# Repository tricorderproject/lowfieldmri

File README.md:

lowfieldmri
======

Experiments in Earth's field magnetic resonance imaging<br>

**DISCLAIMER OF WARRANTIES AND LIMITATION OF LIABILITY.**

UNLESS OTHERWISE SEPARATELY UNDERTAKEN BY THE LICENSOR, TO THE MAXIMUM EXTENT POSSIBLE, THE LICENSOR OFFERS THE LICENSED MATERIAL AS-IS AND AS-AVAILABLE, AND MAKES NO REPRESENTATIONS OR WARRANTIES OF ANY KIND CONCERNING THE LICENSED MATERIAL, WHETHER EXPRESS, IMPLIED, STATUTORY, OR OTHER. THIS INCLUDES, WITHOUT LIMITATION, WARRANTIES OF TITLE, MERCHANTABILITY, FITNESS FOR A PARTICULAR PURPOSE, NON-INFRINGEMENT, ABSENCE OF LATENT OR OTHER DEFECTS, ACCURACY, SAFETY, OR THE PRESENCE OR ABSENCE OF ERRORS, WHETHER OR NOT KNOWN OR DISCOVERABLE. WHERE DISCLAIMERS OF WARRANTIES ARE NOT ALLOWED IN FULL OR IN PART, THIS DISCLAIMER MAY NOT APPLY TO YOU.

TO THE EXTENT POSSIBLE, IN NO EVENT WILL THE LICENSOR BE LIABLE TO YOU ON ANY LEGAL THEORY (INCLUDING, WITHOUT LIMITATION, NEGLIGENCE) OR OTHERWISE FOR ANY DIRECT, SPECIAL, INDIRECT, INCIDENTAL, CONSEQUENTIAL, PUNITIVE, EXEMPLARY, OR OTHER LOSSES, COSTS, EXPENSES, OR DAMAGES ARISING OUT OF THIS PUBLIC LICENSE OR USE OF THE LICENSED MATERIAL, EVEN IF THE LICENSOR HAS BEEN ADVISED OF THE POSSIBILITY OF SUCH LOSSES, COSTS, EXPENSES, OR DAMAGES. WHERE A LIMITATION OF LIABILITY IS NOT ALLOWED IN FULL OR IN PART, THIS LIMITATION MAY NOT APPLY TO YOU.

THE DISCLAIMER OF WARRANTIES AND LIMITATION OF LIABILITY PROVIDED ABOVE SHALL BE INTERPRETED IN A MANNER THAT, TO THE EXTENT POSSIBLE, MOST CLOSELY APPROXIMATES AN ABSOLUTE DISCLAIMER AND WAIVER OF ALL LIABILITY.

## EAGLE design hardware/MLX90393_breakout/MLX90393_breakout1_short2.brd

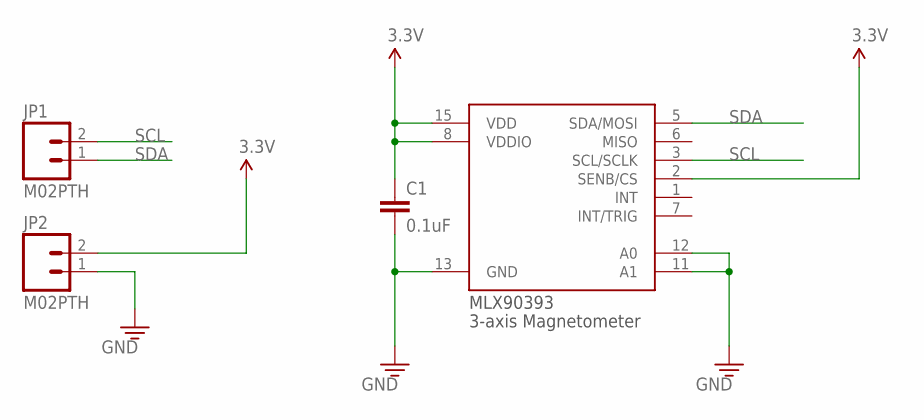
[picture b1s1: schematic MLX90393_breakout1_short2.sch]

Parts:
C1: 0.1uF; 0603
JP1, JP2: M02PTH; 1X02
U$1: MLX90393; 16-QFN

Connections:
3.3V: C1.1, JP2.2, U$1.2 (SENB/CS), U$1.8 (VDDIO), U$1.15 (VDD)
GND: C1.2, JP2.1, U$1.11 (A1), U$1.12 (A0), U$1.13 (GND)
SCL: JP1.2, U$1.3 (SCL/SCLK)
SDA: JP1.1, U$1.5 (SDA/MOSI)

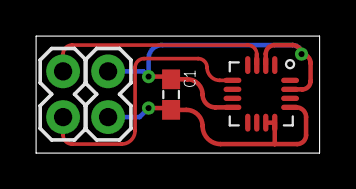
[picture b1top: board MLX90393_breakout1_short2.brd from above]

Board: 2 copper layers, 15.8 x 6.5 mm, 4 parts (0 on the bottom side), 4 nets.

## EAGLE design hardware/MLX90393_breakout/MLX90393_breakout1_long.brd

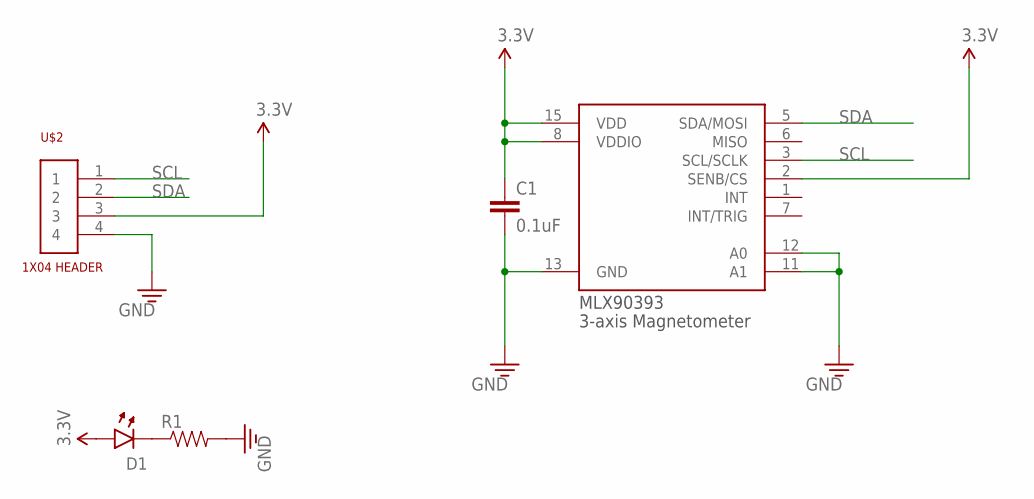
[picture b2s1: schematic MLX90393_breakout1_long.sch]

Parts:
C1: 0.1uF; 0603
D1: 0605-LED; 0603-LED
R1: RESISTOR0603; 0603
U$1: MLX90393; 16-QFN
U$2: 1X04

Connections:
3.3V: C1.1, D1.ANODE, U$1.2 (SENB/CS), U$1.8 (VDDIO), U$1.15 (VDD), U$2.3
GND: C1.2, R1.2, U$1.11 (A1), U$1.12 (A0), U$1.13 (GND), U$2.4
unnamed: D1.CATHODE, R1.1
SCL: U$1.3 (SCL/SCLK), U$2.1
SDA: U$1.5 (SDA/MOSI), U$2.2

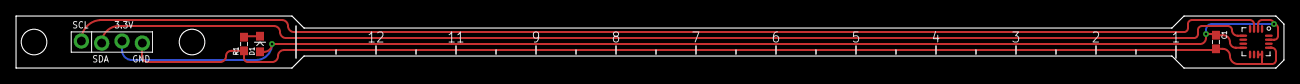
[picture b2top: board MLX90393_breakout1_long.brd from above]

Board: 2 copper layers, 158.5 x 6.5 mm, 5 parts (0 on the bottom side), 5 nets.

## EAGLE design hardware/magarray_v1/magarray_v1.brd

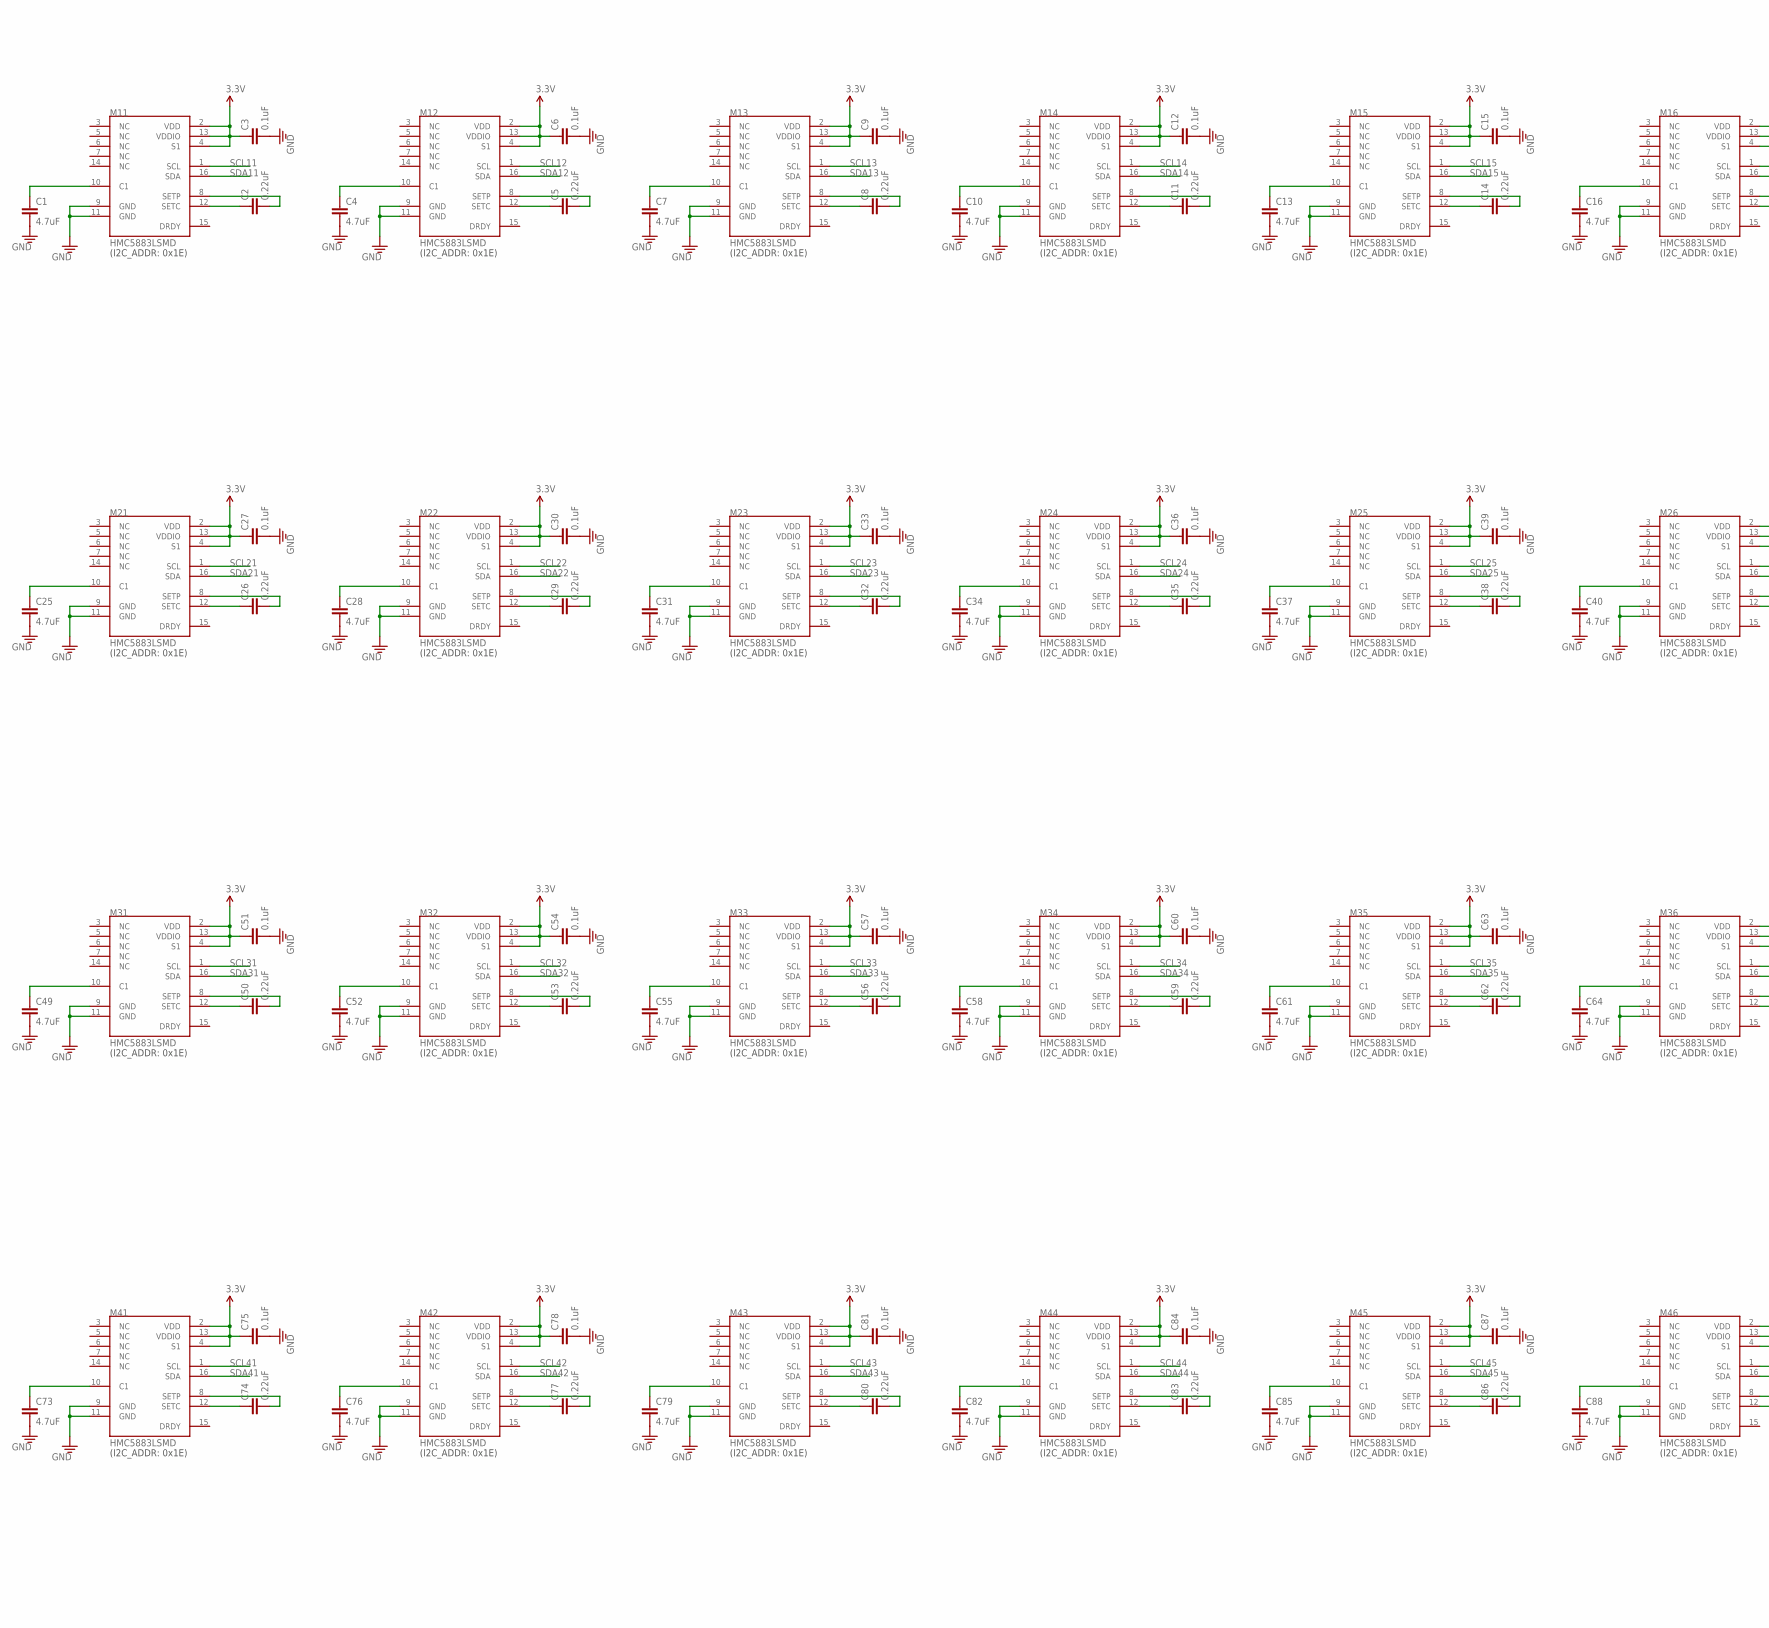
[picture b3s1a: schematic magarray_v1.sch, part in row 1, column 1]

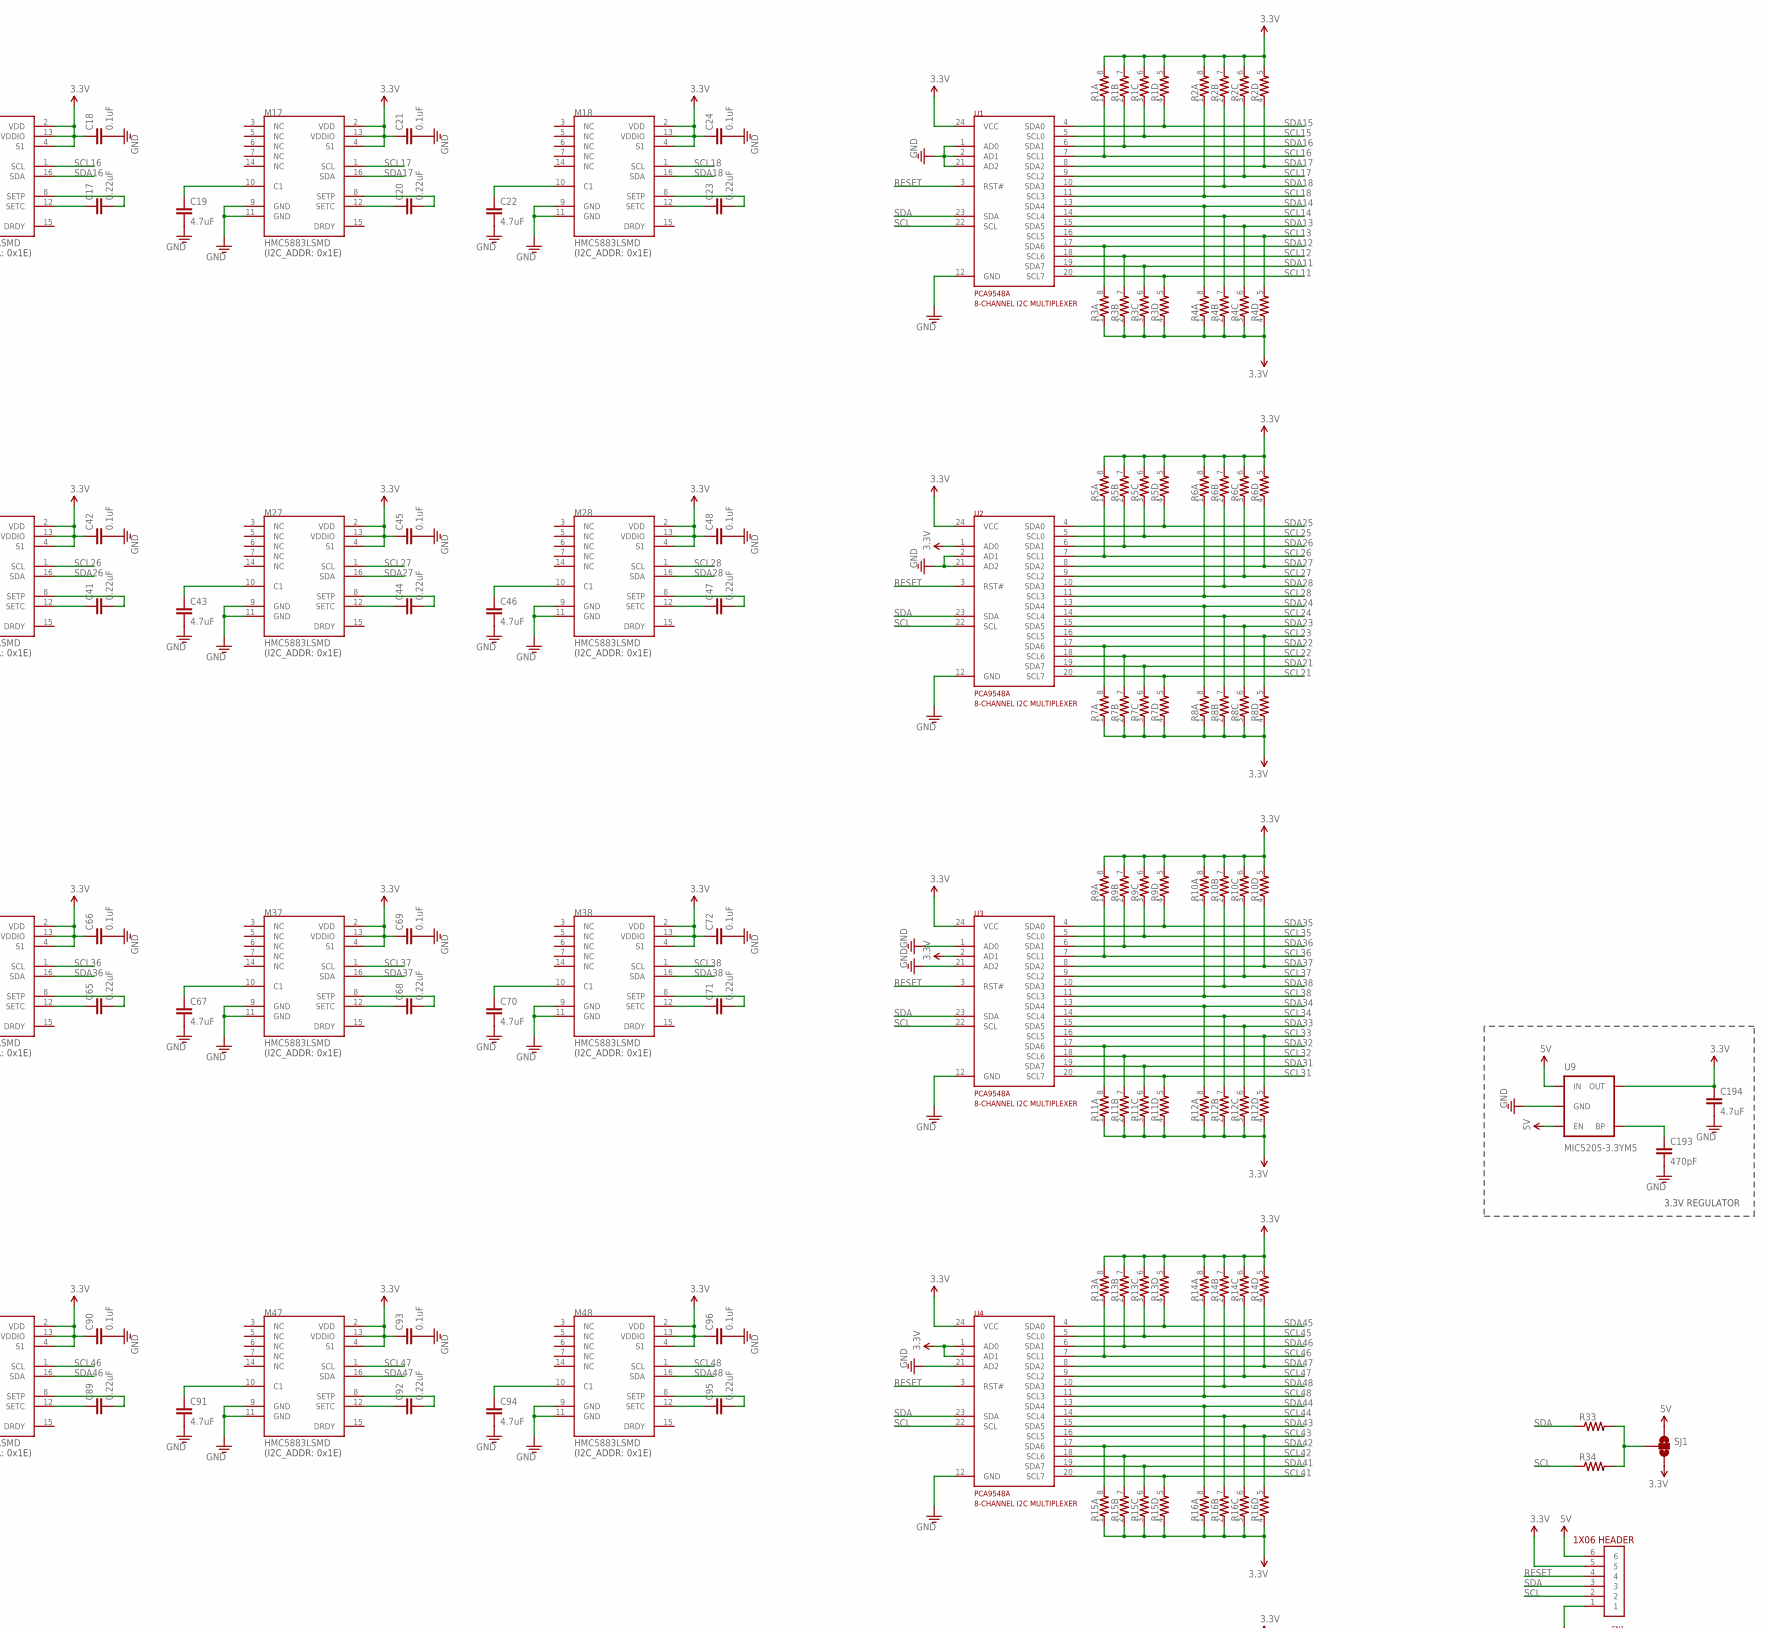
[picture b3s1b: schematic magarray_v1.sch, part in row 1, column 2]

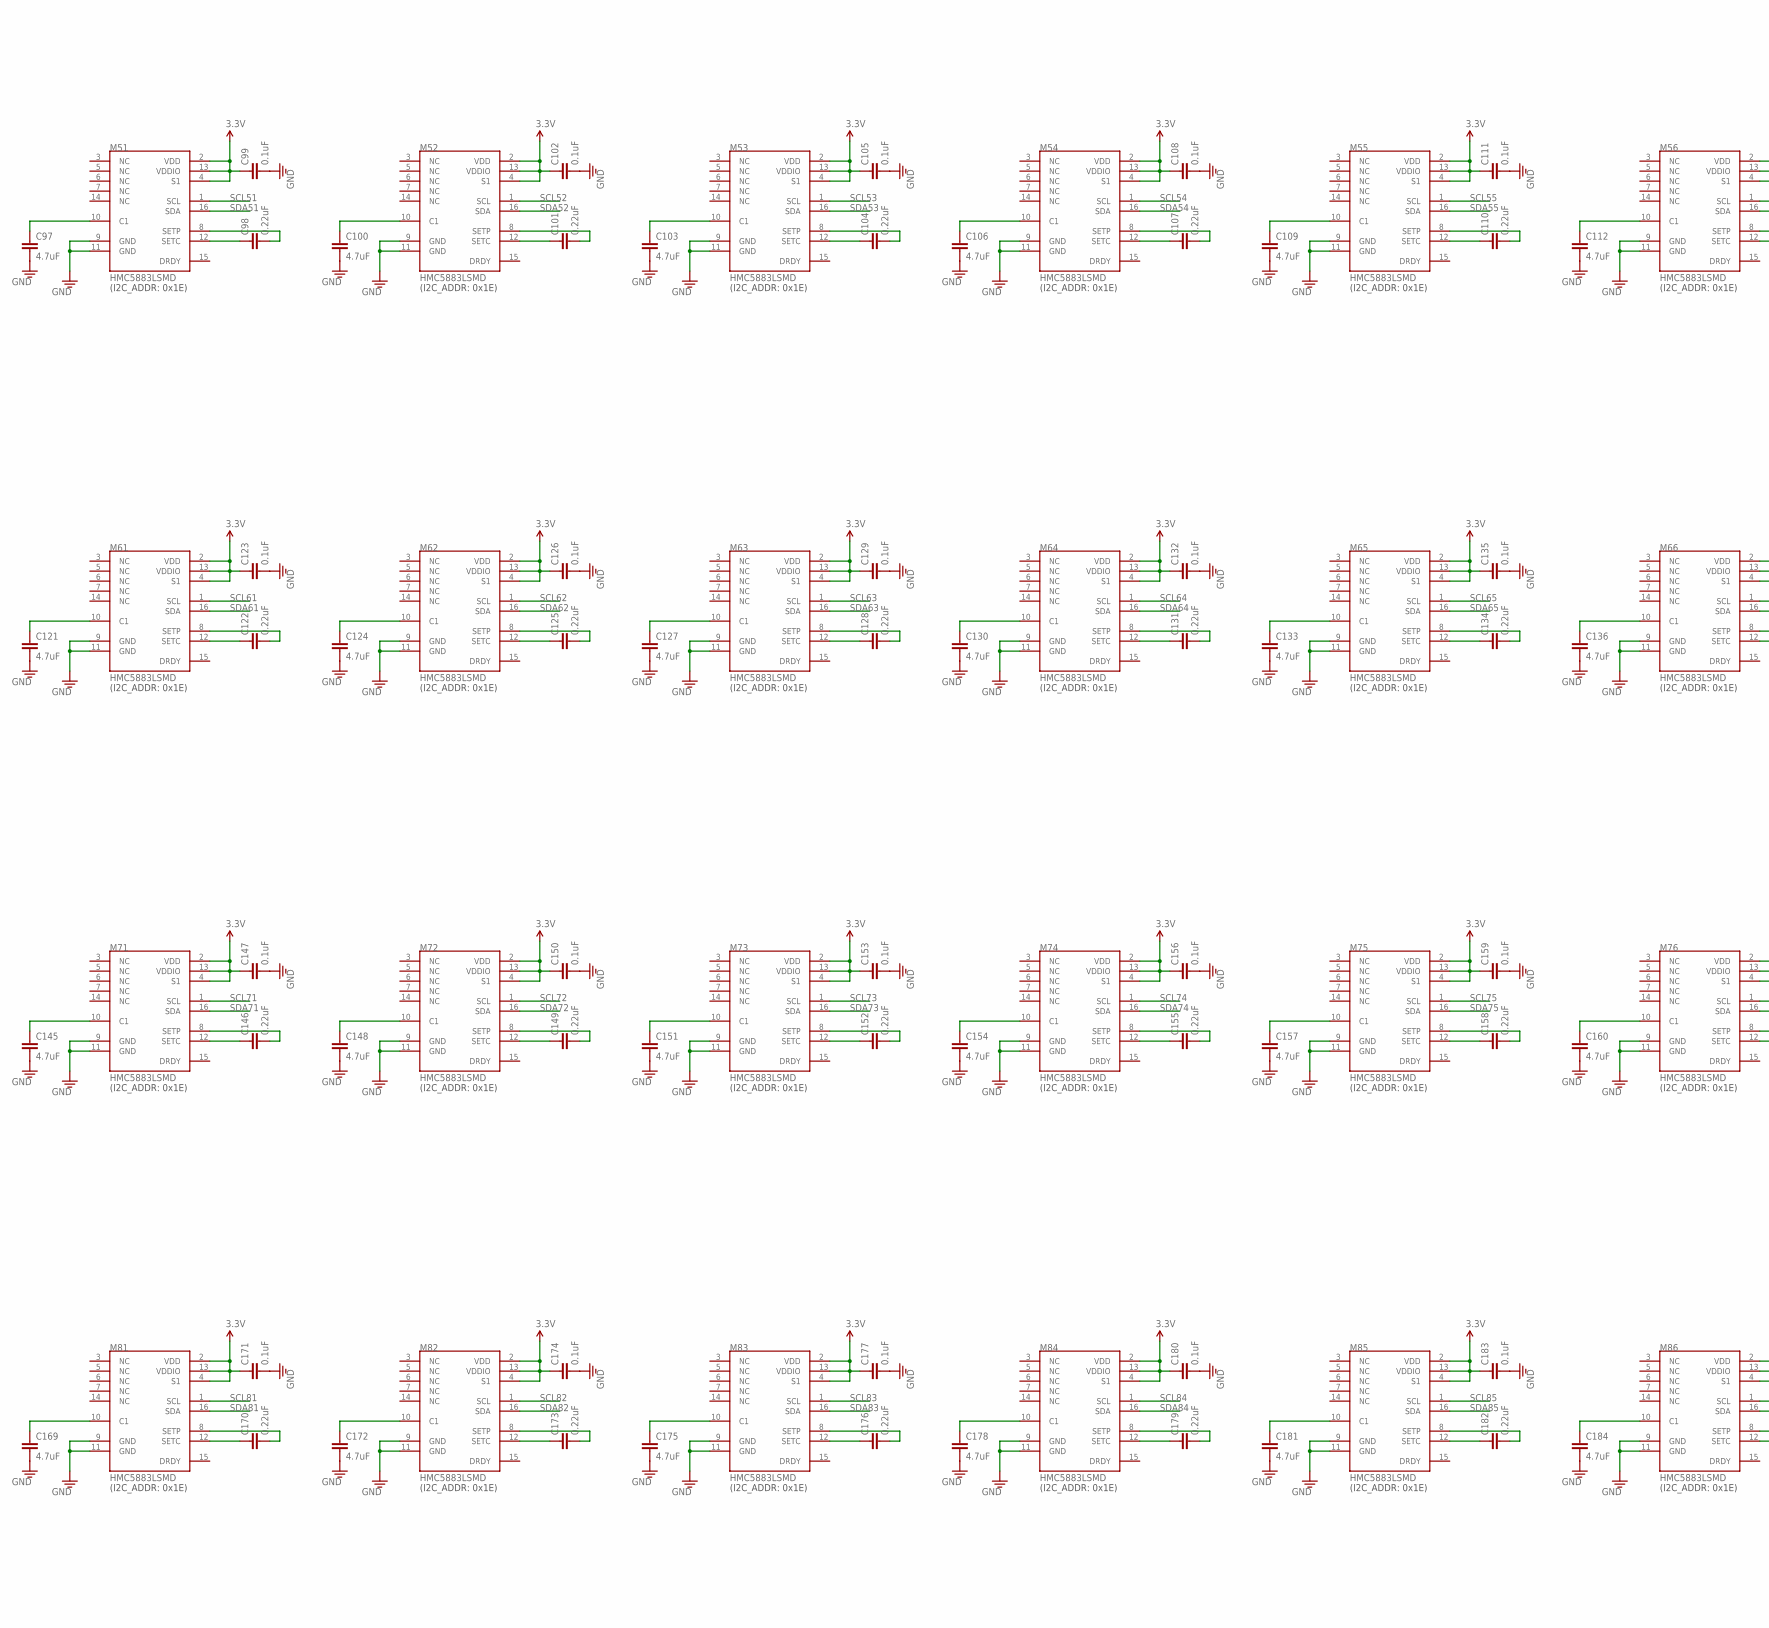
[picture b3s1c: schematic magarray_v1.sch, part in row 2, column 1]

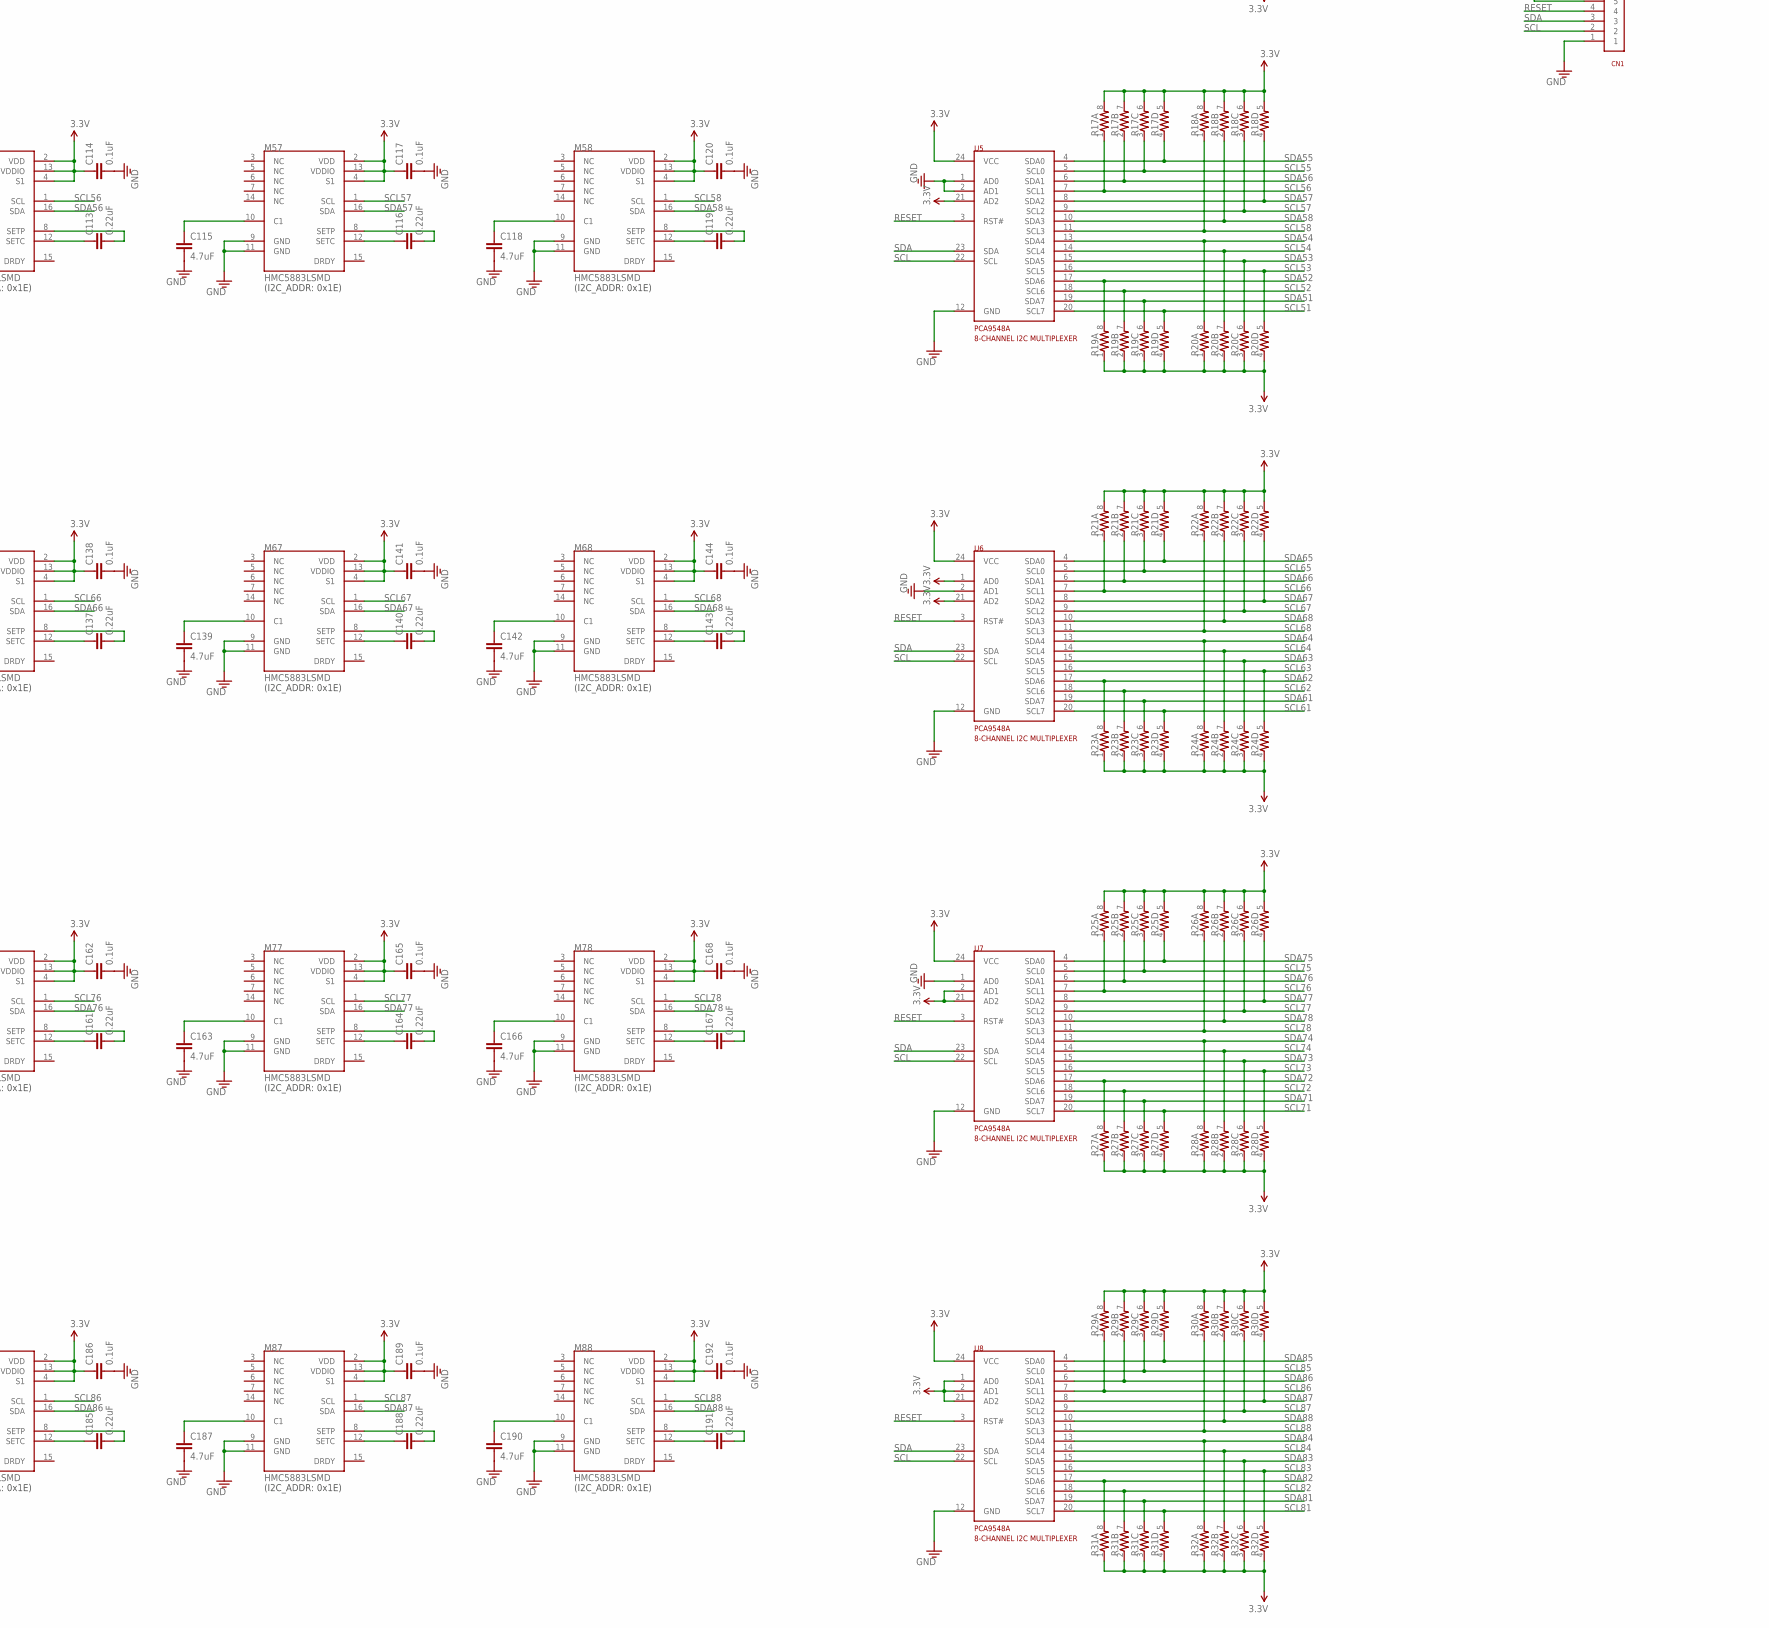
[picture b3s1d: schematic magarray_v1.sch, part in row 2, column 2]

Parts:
C1, C4, C7, C10, C13, C16, C19, C22, C25, C28, C31, C34, C37, C40, C43, C46, C49, C52, C55, C58, C61, C64, C67, C70, C73, C76, C79, C82, C85, C88, C91, C94, C97, C100, C103, C106, C109, C112, C115, C118, C121, C124, C127, C130, C133, C136, C139, C142, C145, C148, C151, C154, C157, C160, C163, C166, C169, C172, C175, C178, C181, C184, C187, C190: 4.7uF; 0603
C2, C5, C8, C11, C14, C17, C20, C23, C26, C29, C32, C35, C38, C41, C44, C47, C50, C53, C56, C59, C62, C65, C68, C71, C74, C77, C80, C83, C86, C89, C92, C95, C98, C101, C104, C107, C110, C113, C116, C119, C122, C125, C128, C131, C134, C137, C140, C143, C146, C149, C152, C155, C158, C161, C164, C167, C170, C173, C176, C179, C182, C185, C188, C191: 0.22uF; C0402
C3, C6, C9, C12, C15, C18, C21, C24, C27, C30, C33, C36, C39, C42, C45, C48, C51, C54, C57, C60, C63, C66, C69, C72, C75, C78, C81, C84, C87, C90, C93, C96, C99, C102, C105, C108, C111, C114, C117, C120, C123, C126, C129, C132, C135, C138, C141, C144, C147, C150, C153, C156, C159, C162, C165, C168, C171, C174, C177, C180, C183, C186, C189, C192: 0.1uF; C0402
C193: 470pF; C0402
C194: 4.7uF; C0402
CN1: 1X06
M11, M12, M13, M14, M15, M16, M17, M18, M21, M22, M23, M24, M25, M26, M27, M28, M31, M32, M33, M34, M35, M36, M37, M38, M41, M42, M43, M44, M45, M46, M47, M48, M51, M52, M53, M54, M55, M56, M57, M58, M61, M62, M63, M64, M65, M66, M67, M68, M71, M72, M73, M74, M75, M76, M77, M78, M81, M82, M83, M84, M85, M86, M87, M88: HMC5883LSMD; 16LPCC
R1, R2, R3, R4, R5, R6, R7, R8, R9, R10, R11, R12, R13, R14, R15, R16, R17, R18, R19, R20, R21, R22, R23, R24, R25, R26, R27, R28, R29, R30, R31, R32: RESISTOR-ARRAY0603-ARV; 0603-ARV
R33, R34: RESISTOR0603; 0603
SJ1: SOLDERJUMPER_2WAYPASTE1&2; SJ_3_PASTE1&2
U1, U2, U3, U4, U5, U6, U7, U8: TCA9548A; TSSOP-24-4.4MM
U9: MIC5205-3.3YM5; SOT23-5

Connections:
3.3V: C3.1, C6.1, C9.1, C12.1, C15.1, C18.1, C21.1, C24.1, C27.1, C30.1, C33.1, C36.1, C39.1, C42.1, C45.1, C48.1, C51.1, C54.1, C57.1, C60.1, C63.1, C66.1, C69.1, C72.1, C75.1, C78.1, C81.1, C84.1, C87.1, C90.1, C93.1, C96.1, C99.1, C102.1, C105.1, C108.1, C111.1, C114.1, C117.1, C120.1, C123.1, C126.1, C129.1, C132.1, C135.1, C138.1, C141.1, C144.1, C147.1, C150.1, C153.1, C156.1, C159.1, C162.1, C165.1, C168.1, C171.1, C174.1, C177.1, C180.1, C183.1, C186.1, C189.1, C192.1, C194.1, CN1.5, M11.2 (VDD), M11.4 (S1), M11.13 (VDDIO), M12.2 (VDD), M12.4 (S1), M12.13 (VDDIO), M13.2 (VDD), M13.4 (S1), M13.13 (VDDIO), M14.2 (VDD), M14.4 (S1), M14.13 (VDDIO), M15.2 (VDD), M15.4 (S1), M15.13 (VDDIO), M16.2 (VDD), M16.4 (S1), M16.13 (VDDIO), M17.2 (VDD), M17.4 (S1), M17.13 (VDDIO), M18.2 (VDD), M18.4 (S1), M18.13 (VDDIO), M21.2 (VDD), M21.4 (S1), M21.13 (VDDIO), M22.2 (VDD), M22.4 (S1), M22.13 (VDDIO), M23.2 (VDD), M23.4 (S1), M23.13 (VDDIO), M24.2 (VDD), M24.4 (S1), M24.13 (VDDIO), M25.2 (VDD), M25.4 (S1), M25.13 (VDDIO), M26.2 (VDD), M26.4 (S1), M26.13 (VDDIO), M27.2 (VDD), M27.4 (S1), M27.13 (VDDIO), M28.2 (VDD), M28.4 (S1), M28.13 (VDDIO), M31.2 (VDD), M31.4 (S1), M31.13 (VDDIO), M32.2 (VDD), M32.4 (S1), M32.13 (VDDIO), M33.2 (VDD), M33.4 (S1), M33.13 (VDDIO), M34.2 (VDD), M34.4 (S1), M34.13 (VDDIO), M35.2 (VDD), M35.4 (S1), M35.13 (VDDIO), M36.2 (VDD), M36.4 (S1), M36.13 (VDDIO), M37.2 (VDD), M37.4 (S1), M37.13 (VDDIO), M38.2 (VDD), M38.4 (S1), M38.13 (VDDIO), M41.2 (VDD), M41.4 (S1), M41.13 (VDDIO), M42.2 (VDD), M42.4 (S1), M42.13 (VDDIO), M43.2 (VDD), M43.4 (S1), M43.13 (VDDIO), M44.2 (VDD), M44.4 (S1), M44.13 (VDDIO), M45.2 (VDD), M45.4 (S1), M45.13 (VDDIO), M46.2 (VDD), M46.4 (S1), M46.13 (VDDIO), M47.2 (VDD), M47.4 (S1), M47.13 (VDDIO), M48.2 (VDD)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
5V: CN1.6, SJ1.1, U9.1 (IN), U9.3 (EN)
GND: C1.2, C3.2, C4.2, C6.2, C7.2, C9.2, C10.2, C12.2, C13.2, C15.2, C16.2, C18.2, C19.2, C21.2, C22.2, C24.2, C25.2, C27.2, C28.2, C30.2, C31.2, C33.2, C34.2, C36.2, C37.2, C39.2, C40.2, C42.2, C43.2, C45.2, C46.2, C48.2, C49.2, C51.2, C52.2, C54.2, C55.2, C57.2, C58.2, C60.2, C61.2, C63.2, C64.2, C66.2, C67.2, C69.2, C70.2, C72.2, C73.2, C75.2, C76.2, C78.2, C79.2, C81.2, C82.2, C84.2, C85.2, C87.2, C88.2, C90.2, C91.2, C93.2, C94.2, C96.2, C97.2, C99.2, C100.2, C102.2, C103.2, C105.2, C106.2, C108.2, C109.2, C111.2, C112.2, C114.2, C115.2, C117.2, C118.2, C120.2, C121.2, C123.2, C124.2, C126.2, C127.2, C129.2, C130.2, C132.2, C133.2, C135.2, C136.2, C138.2, C139.2, C141.2, C142.2, C144.2, C145.2, C147.2, C148.2, C150.2, C151.2, C153.2, C154.2, C156.2, C157.2, C159.2, C160.2, C162.2, C163.2, C165.2, C166.2, C168.2, C169.2, C171.2, C172.2, C174.2, C175.2, C177.2, C178.2, C180.2, C181.2, C183.2, C184.2, C186.2, C187.2, C189.2, C190.2, C192.2, C193.2, C194.2, CN1.1, M11.9 (GND), M11.11 (GND), M12.9 (GND), M12.11 (GND), M13.9 (GND), M13.11 (GND), M14.9 (GND), M14.11 (GND), M15.9 (GND), M15.11 (GND), M16.9 (GND), M16.11 (GND), M17.9 (GND), M17.11 (GND), M18.9 (GND), M18.11 (GND), M21.9 (GND), M21.11 (GND), M22.9 (GND), M22.11 (GND), M23.9 (GND), M23.11 (GND), M24.9 (GND), M24.11 (GND), M25.9 (GND), M25.11 (GND), M26.9 (GND), M26.11 (GND), M27.9 (GND)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
unnamed: C4.1, M12.10 (C1)
unnamed: C5.1, M12.12 (SETC)
unnamed: C5.2, M12.8 (SETP)
unnamed: C7.1, M13.10 (C1)
unnamed: C8.1, M13.12 (SETC)
unnamed: C1.1, M11.10 (C1)
unnamed: C8.2, M13.8 (SETP)
unnamed: C10.1, M14.10 (C1)
unnamed: C2.1, M11.12 (SETC)
unnamed: C2.2, M11.8 (SETP)
unnamed: C11.1, M14.12 (SETC)
unnamed: C11.2, M14.8 (SETP)
unnamed: C13.1, M15.10 (C1)
unnamed: C14.1, M15.12 (SETC)
unnamed: C14.2, M15.8 (SETP)
unnamed: C16.1, M16.10 (C1)
unnamed: C17.1, M16.12 (SETC)
unnamed: C17.2, M16.8 (SETP)
unnamed: C19.1, M17.10 (C1)
unnamed: C20.1, M17.12 (SETC)
unnamed: C20.2, M17.8 (SETP)
unnamed: C22.1, M18.10 (C1)
unnamed: C23.1, M18.12 (SETC)
unnamed: C23.2, M18.8 (SETP)
unnamed: C25.1, M21.10 (C1)
unnamed: C26.1, M21.12 (SETC)
unnamed: C26.2, M21.8 (SETP)
unnamed: C28.1, M22.10 (C1)
unnamed: C29.1, M22.12 (SETC)
unnamed: C29.2, M22.8 (SETP)
unnamed: C31.1, M23.10 (C1)
unnamed: C32.1, M23.12 (SETC)
unnamed: C32.2, M23.8 (SETP)
unnamed: C34.1, M24.10 (C1)
unnamed: C35.1, M24.12 (SETC)
unnamed: C35.2, M24.8 (SETP)
unnamed: C37.1, M25.10 (C1)
unnamed: C38.1, M25.12 (SETC)
unnamed: C38.2, M25.8 (SETP)
unnamed: C40.1, M26.10 (C1)
unnamed: C41.1, M26.12 (SETC)
unnamed: C41.2, M26.8 (SETP)
unnamed: C43.1, M27.10 (C1)
unnamed: C44.1, M27.12 (SETC)
unnamed: C44.2, M27.8 (SETP)
unnamed: C46.1, M28.10 (C1)
unnamed: C47.1, M28.12 (SETC)
unnamed: C47.2, M28.8 (SETP)
unnamed: C49.1, M31.10 (C1)
unnamed: C50.1, M31.12 (SETC)
unnamed: C50.2, M31.8 (SETP)
unnamed: C52.1, M32.10 (C1)
unnamed: C53.1, M32.12 (SETC)
unnamed: C53.2, M32.8 (SETP)
unnamed: C55.1, M33.10 (C1)
unnamed: C56.1, M33.12 (SETC)
unnamed: C56.2, M33.8 (SETP)
unnamed: C58.1, M34.10 (C1)
unnamed: C59.1, M34.12 (SETC)
unnamed: C59.2, M34.8 (SETP)
unnamed: C61.1, M35.10 (C1)
unnamed: C62.1, M35.12 (SETC)
unnamed: C62.2, M35.8 (SETP)
unnamed: C64.1, M36.10 (C1)
unnamed: C65.1, M36.12 (SETC)
unnamed: C65.2, M36.8 (SETP)
unnamed: C67.1, M37.10 (C1)
unnamed: C68.1, M37.12 (SETC)
unnamed: C68.2, M37.8 (SETP)
unnamed: C70.1, M38.10 (C1)
unnamed: C71.1, M38.12 (SETC)
unnamed: C71.2, M38.8 (SETP)
unnamed: C73.1, M41.10 (C1)
unnamed: C74.1, M41.12 (SETC)
unnamed: C74.2, M41.8 (SETP)
unnamed: C76.1, M42.10 (C1)
unnamed: C77.1, M42.12 (SETC)
unnamed: C77.2, M42.8 (SETP)
unnamed: C79.1, M43.10 (C1)
unnamed: C80.1, M43.12 (SETC)
unnamed: C80.2, M43.8 (SETP)
unnamed: C82.1, M44.10 (C1)
unnamed: C83.1, M44.12 (SETC)
unnamed: C83.2, M44.8 (SETP)
unnamed: C85.1, M45.10 (C1)
unnamed: C86.1, M45.12 (SETC)
unnamed: C86.2, M45.8 (SETP)
unnamed: C88.1, M46.10 (C1)
unnamed: C89.1, M46.12 (SETC)
unnamed: C89.2, M46.8 (SETP)
unnamed: C91.1, M47.10 (C1)
unnamed: C92.1, M47.12 (SETC)
unnamed: C92.2, M47.8 (SETP)
unnamed: C94.1, M48.10 (C1)
unnamed: C95.1, M48.12 (SETC)
unnamed: C95.2, M48.8 (SETP)
unnamed: C97.1, M51.10 (C1)
unnamed: C98.1, M51.12 (SETC)
unnamed: C98.2, M51.8 (SETP)
unnamed: C100.1, M52.10 (C1)
unnamed: C101.1, M52.12 (SETC)
unnamed: C101.2, M52.8 (SETP)
unnamed: C103.1, M53.10 (C1)
unnamed: C104.1, M53.12 (SETC)
unnamed: C104.2, M53.8 (SETP)
unnamed: C106.1, M54.10 (C1)
unnamed: C107.1, M54.12 (SETC)
unnamed: C107.2, M54.8 (SETP)
unnamed: C109.1, M55.10 (C1)
unnamed: C110.1, M55.12 (SETC)
unnamed: C110.2, M55.8 (SETP)
unnamed: C112.1, M56.10 (C1)
unnamed: C113.1, M56.12 (SETC)
unnamed: C113.2, M56.8 (SETP)
unnamed: C115.1, M57.10 (C1)
unnamed: C116.1, M57.12 (SETC)
unnamed: C116.2, M57.8 (SETP)
unnamed: C118.1, M58.10 (C1)
unnamed: C119.1, M58.12 (SETC)
unnamed: C119.2, M58.8 (SETP)
unnamed: C121.1, M61.10 (C1)
unnamed: C122.1, M61.12 (SETC)
unnamed: C122.2, M61.8 (SETP)
unnamed: C124.1, M62.10 (C1)
unnamed: C125.1, M62.12 (SETC)
unnamed: C125.2, M62.8 (SETP)
unnamed: C127.1, M63.10 (C1)
unnamed: C128.1, M63.12 (SETC)
unnamed: C128.2, M63.8 (SETP)
unnamed: C130.1, M64.10 (C1)
unnamed: C131.1, M64.12 (SETC)
unnamed: C131.2, M64.8 (SETP)
unnamed: C133.1, M65.10 (C1)
unnamed: C134.1, M65.12 (SETC)
unnamed: C134.2, M65.8 (SETP)
unnamed: C136.1, M66.10 (C1)
unnamed: C137.1, M66.12 (SETC)
unnamed: C137.2, M66.8 (SETP)
unnamed: C139.1, M67.10 (C1)
unnamed: C140.1, M67.12 (SETC)
unnamed: C140.2, M67.8 (SETP)
unnamed: C142.1, M68.10 (C1)
unnamed: C143.1, M68.12 (SETC)
unnamed: C143.2, M68.8 (SETP)
unnamed: C145.1, M71.10 (C1)
unnamed: C146.1, M71.12 (SETC)
unnamed: C146.2, M71.8 (SETP)
unnamed: C148.1, M72.10 (C1)
unnamed: C149.1, M72.12 (SETC)
unnamed: C149.2, M72.8 (SETP)
unnamed: C151.1, M73.10 (C1)
unnamed: C152.1, M73.12 (SETC)
unnamed: C152.2, M73.8 (SETP)
unnamed: C154.1, M74.10 (C1)
unnamed: C155.1, M74.12 (SETC)
unnamed: C155.2, M74.8 (SETP)
unnamed: C157.1, M75.10 (C1)
unnamed: C158.1, M75.12 (SETC)
unnamed: C158.2, M75.8 (SETP)
unnamed: C160.1, M76.10 (C1)
unnamed: C161.1, M76.12 (SETC)
unnamed: C161.2, M76.8 (SETP)
unnamed: C163.1, M77.10 (C1)
unnamed: C164.1, M77.12 (SETC)
unnamed: C164.2, M77.8 (SETP)
unnamed: C166.1, M78.10 (C1)
unnamed: C167.1, M78.12 (SETC)
unnamed: C167.2, M78.8 (SETP)
unnamed: C169.1, M81.10 (C1)
unnamed: C170.1, M81.12 (SETC)
unnamed: C170.2, M81.8 (SETP)
unnamed: C172.1, M82.10 (C1)
unnamed: C173.1, M82.12 (SETC)
unnamed: C173.2, M82.8 (SETP)
unnamed: C175.1, M83.10 (C1)
unnamed: C176.1, M83.12 (SETC)
unnamed: C176.2, M83.8 (SETP)
unnamed: C178.1, M84.10 (C1)
unnamed: C179.1, M84.12 (SETC)
unnamed: C179.2, M84.8 (SETP)
unnamed: C181.1, M85.10 (C1)
unnamed: C182.1, M85.12 (SETC)
unnamed: C182.2, M85.8 (SETP)
unnamed: C184.1, M86.10 (C1)
unnamed: C185.1, M86.12 (SETC)
unnamed: C185.2, M86.8 (SETP)
unnamed: C187.1, M87.10 (C1)
unnamed: C188.1, M87.12 (SETC)
unnamed: C188.2, M87.8 (SETP)
unnamed: C190.1, M88.10 (C1)
unnamed: C191.1, M88.12 (SETC)
unnamed: C191.2, M88.8 (SETP)
unnamed: C193.1, U9.4 (BP)
unnamed: R33.2, R34.2, SJ1.2
RESET: CN1.4, U1.3 (RST#), U2.3 (RST#), U3.3 (RST#), U4.3 (RST#), U5.3 (RST#), U6.3 (RST#), U7.3 (RST#), U8.3 (RST#)
SCL: CN1.2, R34.1, U1.22 (SCL), U2.22 (SCL), U3.22 (SCL), U4.22 (SCL), U5.22 (SCL), U6.22 (SCL), U7.22 (SCL), U8.22 (SCL)
SCL11: M11.1 (SCL), R3.5 (2), U1.20 (SCL7)
SCL12: M12.1 (SCL), R3.7 (2), U1.18 (SCL6)
SCL13: M13.1 (SCL), R4.5 (2), U1.16 (SCL5)
SCL14: M14.1 (SCL), R4.7 (2), U1.14 (SCL4)
SCL15: M15.1 (SCL), R1.3 (1), U1.5 (SCL0)
SCL16: M16.1 (SCL), R1.1, U1.7 (SCL1)
SCL17: M17.1 (SCL), R2.3 (1), U1.9 (SCL2)
SCL18: M18.1 (SCL), R2.1, U1.11 (SCL3)
SCL21: M21.1 (SCL), R7.5 (2), U2.20 (SCL7)
SCL22: M22.1 (SCL), R7.7 (2), U2.18 (SCL6)
SCL23: M23.1 (SCL), R8.5 (2), U2.16 (SCL5)
SCL24: M24.1 (SCL), R8.7 (2), U2.14 (SCL4)
SCL25: M25.1 (SCL), R5.3 (1), U2.5 (SCL0)
SCL26: M26.1 (SCL), R5.1, U2.7 (SCL1)
SCL27: M27.1 (SCL), R6.3 (1), U2.9 (SCL2)
SCL28: M28.1 (SCL), R6.1, U2.11 (SCL3)
SCL31: M31.1 (SCL), R11.5 (2), U3.20 (SCL7)
SCL32: M32.1 (SCL), R11.7 (2), U3.18 (SCL6)
SCL33: M33.1 (SCL), R12.5 (2), U3.16 (SCL5)
SCL34: M34.1 (SCL), R12.7 (2), U3.14 (SCL4)
SCL35: M35.1 (SCL), R9.3 (1), U3.5 (SCL0)
SCL36: M36.1 (SCL), R9.1, U3.7 (SCL1)
SCL37: M37.1 (SCL), R10.3 (1), U3.9 (SCL2)
SCL38: M38.1 (SCL), R10.1, U3.11 (SCL3)
SCL41: M41.1 (SCL), R15.5 (2), U4.20 (SCL7)
SCL42: M42.1 (SCL), R15.7 (2), U4.18 (SCL6)
SCL43: M43.1 (SCL), R16.5 (2), U4.16 (SCL5)
SCL44: M44.1 (SCL), R16.7 (2), U4.14 (SCL4)
SCL45: M45.1 (SCL), R13.3 (1), U4.5 (SCL0)
SCL46: M46.1 (SCL), R13.1, U4.7 (SCL1)
SCL47: M47.1 (SCL), R14.3 (1), U4.9 (SCL2)
SCL48: M48.1 (SCL), R14.1, U4.11 (SCL3)
SCL51: M51.1 (SCL), R19.5 (2), U5.20 (SCL7)
SCL52: M52.1 (SCL), R19.7 (2), U5.18 (SCL6)
SCL53: M53.1 (SCL), R20.5 (2), U5.16 (SCL5)
SCL54: M54.1 (SCL), R20.7 (2), U5.14 (SCL4)
SCL55: M55.1 (SCL), R17.3 (1), U5.5 (SCL0)
SCL56: M56.1 (SCL), R17.1, U5.7 (SCL1)
SCL57: M57.1 (SCL), R18.3 (1), U5.9 (SCL2)
SCL58: M58.1 (SCL), R18.1, U5.11 (SCL3)
SCL61: M61.1 (SCL), R23.5 (2), U6.20 (SCL7)
SCL62: M62.1 (SCL), R23.7 (2), U6.18 (SCL6)
SCL63: M63.1 (SCL), R24.5 (2), U6.16 (SCL5)
SCL64: M64.1 (SCL), R24.7 (2), U6.14 (SCL4)
SCL65: M65.1 (SCL), R21.3 (1), U6.5 (SCL0)
SCL66: M66.1 (SCL), R21.1, U6.7 (SCL1)
SCL67: M67.1 (SCL), R22.3 (1), U6.9 (SCL2)
SCL68: M68.1 (SCL), R22.1, U6.11 (SCL3)
SCL71: M71.1 (SCL), R27.5 (2), U7.20 (SCL7)
SCL72: M72.1 (SCL), R27.7 (2), U7.18 (SCL6)
SCL73: M73.1 (SCL), R28.5 (2), U7.16 (SCL5)
SCL74: M74.1 (SCL), R28.7 (2), U7.14 (SCL4)
SCL75: M75.1 (SCL), R25.3 (1), U7.5 (SCL0)
SCL76: M76.1 (SCL), R25.1, U7.7 (SCL1)
SCL77: M77.1 (SCL), R26.3 (1), U7.9 (SCL2)
SCL78: M78.1 (SCL), R26.1, U7.11 (SCL3)
SCL81: M81.1 (SCL), R31.5 (2), U8.20 (SCL7)
SCL82: M82.1 (SCL), R31.7 (2), U8.18 (SCL6)
SCL83: M83.1 (SCL), R32.5 (2), U8.16 (SCL5)
SCL84: M84.1 (SCL), R32.7 (2), U8.14 (SCL4)
SCL85: M85.1 (SCL), R29.3 (1), U8.5 (SCL0)
SCL86: M86.1 (SCL), R29.1, U8.7 (SCL1)
SCL87: M87.1 (SCL), R30.3 (1), U8.9 (SCL2)
SCL88: M88.1 (SCL), R30.1, U8.11 (SCL3)
SDA: CN1.3, R33.1, U1.23 (SDA), U2.23 (SDA), U3.23 (SDA), U4.23 (SDA), U5.23 (SDA), U6.23 (SDA), U7.23 (SDA), U8.23 (SDA)
SDA11: M11.16 (SDA), R3.6 (2), U1.19 (SDA7)
SDA12: M12.16 (SDA), R3.8 (2), U1.17 (SDA6)
SDA13: M13.16 (SDA), R4.6 (2), U1.15 (SDA5)
SDA14: M14.16 (SDA), R4.8 (2), U1.13 (SDA4)
SDA15: M15.16 (SDA), R1.4 (1), U1.4 (SDA0)
SDA16: M16.16 (SDA), R1.2 (1), U1.6 (SDA1)
SDA17: M17.16 (SDA), R2.4 (1), U1.8 (SDA2)
SDA18: M18.16 (SDA), R2.2 (1), U1.10 (SDA3)
SDA21: M21.16 (SDA), R7.6 (2), U2.19 (SDA7)
SDA22: M22.16 (SDA), R7.8 (2), U2.17 (SDA6)
SDA23: M23.16 (SDA), R8.6 (2), U2.15 (SDA5)
SDA24: M24.16 (SDA), R8.8 (2), U2.13 (SDA4)
SDA25: M25.16 (SDA), R5.4 (1), U2.4 (SDA0)
SDA26: M26.16 (SDA), R5.2 (1), U2.6 (SDA1)
SDA27: M27.16 (SDA), R6.4 (1), U2.8 (SDA2)
SDA28: M28.16 (SDA), R6.2 (1), U2.10 (SDA3)
SDA31: M31.16 (SDA), R11.6 (2), U3.19 (SDA7)
SDA32: M32.16 (SDA), R11.8 (2), U3.17 (SDA6)
SDA33: M33.16 (SDA), R12.6 (2), U3.15 (SDA5)
SDA34: M34.16 (SDA), R12.8 (2), U3.13 (SDA4)
SDA35: M35.16 (SDA), R9.4 (1), U3.4 (SDA0)
SDA36: M36.16 (SDA), R9.2 (1), U3.6 (SDA1)
SDA37: M37.16 (SDA), R10.4 (1), U3.8 (SDA2)
SDA38: M38.16 (SDA), R10.2 (1), U3.10 (SDA3)
SDA41: M41.16 (SDA), R15.6 (2), U4.19 (SDA7)
SDA42: M42.16 (SDA), R15.8 (2), U4.17 (SDA6)
SDA43: M43.16 (SDA), R16.6 (2), U4.15 (SDA5)
SDA44: M44.16 (SDA), R16.8 (2), U4.13 (SDA4)
SDA45: M45.16 (SDA), R13.4 (1), U4.4 (SDA0)
SDA46: M46.16 (SDA), R13.2 (1), U4.6 (SDA1)
SDA47: M47.16 (SDA), R14.4 (1), U4.8 (SDA2)
SDA48: M48.16 (SDA), R14.2 (1), U4.10 (SDA3)
SDA51: M51.16 (SDA), R19.6 (2), U5.19 (SDA7)
SDA52: M52.16 (SDA), R19.8 (2), U5.17 (SDA6)
SDA53: M53.16 (SDA), R20.6 (2), U5.15 (SDA5)
SDA54: M54.16 (SDA), R20.8 (2), U5.13 (SDA4)
SDA55: M55.16 (SDA), R17.4 (1), U5.4 (SDA0)
SDA56: M56.16 (SDA), R17.2 (1), U5.6 (SDA1)
SDA57: M57.16 (SDA), R18.4 (1), U5.8 (SDA2)
SDA58: M58.16 (SDA), R18.2 (1), U5.10 (SDA3)
SDA61: M61.16 (SDA), R23.6 (2), U6.19 (SDA7)
SDA62: M62.16 (SDA), R23.8 (2), U6.17 (SDA6)
SDA63: M63.16 (SDA), R24.6 (2), U6.15 (SDA5)
SDA64: M64.16 (SDA), R24.8 (2), U6.13 (SDA4)
SDA65: M65.16 (SDA), R21.4 (1), U6.4 (SDA0)
SDA66: M66.16 (SDA), R21.2 (1), U6.6 (SDA1)
SDA67: M67.16 (SDA), R22.4 (1), U6.8 (SDA2)
SDA68: M68.16 (SDA), R22.2 (1), U6.10 (SDA3)
SDA71: M71.16 (SDA), R27.6 (2), U7.19 (SDA7)
SDA72: M72.16 (SDA), R27.8 (2), U7.17 (SDA6)
SDA73: M73.16 (SDA), R28.6 (2), U7.15 (SDA5)
SDA74: M74.16 (SDA), R28.8 (2), U7.13 (SDA4)
SDA75: M75.16 (SDA), R25.4 (1), U7.4 (SDA0)
SDA76: M76.16 (SDA), R25.2 (1), U7.6 (SDA1)
SDA77: M77.16 (SDA), R26.4 (1), U7.8 (SDA2)
SDA78: M78.16 (SDA), R26.2 (1), U7.10 (SDA3)
SDA81: M81.16 (SDA), R31.6 (2), U8.19 (SDA7)
SDA82: M82.16 (SDA), R31.8 (2), U8.17 (SDA6)
SDA83: M83.16 (SDA), R32.6 (2), U8.15 (SDA5)
SDA84: M84.16 (SDA), R32.8 (2), U8.13 (SDA4)
SDA85: M85.16 (SDA), R29.4 (1), U8.4 (SDA0)
SDA86: M86.16 (SDA), R29.2 (1), U8.6 (SDA1)
SDA87: M87.16 (SDA), R30.4 (1), U8.8 (SDA2)
SDA88: M88.16 (SDA), R30.2 (1), U8.10 (SDA3)

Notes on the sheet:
(I2C_ADDR: 0x1E)
3.3V REGULATOR

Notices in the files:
parts and their libraries:
arducorder-mini: Licensing: Creative Commons ShareAlike 4.0 International - https://creativecommons.org/licenses/by-sa/4.0
